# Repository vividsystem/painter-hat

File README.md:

# painter-hat
## A stepper motor hat that sucks less.
<div style="display: flex; flex-direction: row;">

</div>

Disclaimer: I haven't gotten the possibility to actually manufacture this yet. Therefore it might not work

Features:
* dual stepper-motor driver control <br>
* 100W USB-C PD to power motors and raspberry pi <br>
* support for A4988, TMC2208, TMC2209, etc. driver modules including UART control <br>
* meant as a replacement for [Waveshare Stepper Motor HAT](https://www.waveshare.com/wiki/Stepper_Motor_HAT)<sup>*</sup> <br><br><br>

<sup>*</sup>not completely hot-swap. you will have to use a different firmware

## Motivation 
I was very frustrated working with the [Waveshare Stepper Motor HAT](https://www.waveshare.com/wiki/Stepper_Motor_HAT).
The quality control seems to be off as two HATs I ordered didn't work. 
Their documentation is good and the provided codes works but there are some minor issues that led me to write my own code to
control the hat. Most importantly you can't swap drivers (in case you fry them for example) which led me to buy multiple
new drivers after testing and subsequently frying the drivers. This sucks because for my use case I have to get a whole
new HAT even when one of the two drivers is still working.

## Schematic

## PCB
### Top Layer - Signal

### 1st Internal Layer - Ground 

### 2nd Internal Layer - Power 

### Bottom Layer - Signal with GND Copper Fill 

## DIY it
It is about 155.58€ for the minimum PCBA PCB amount on JLCPCB.

## Firmware
Currently outdated!

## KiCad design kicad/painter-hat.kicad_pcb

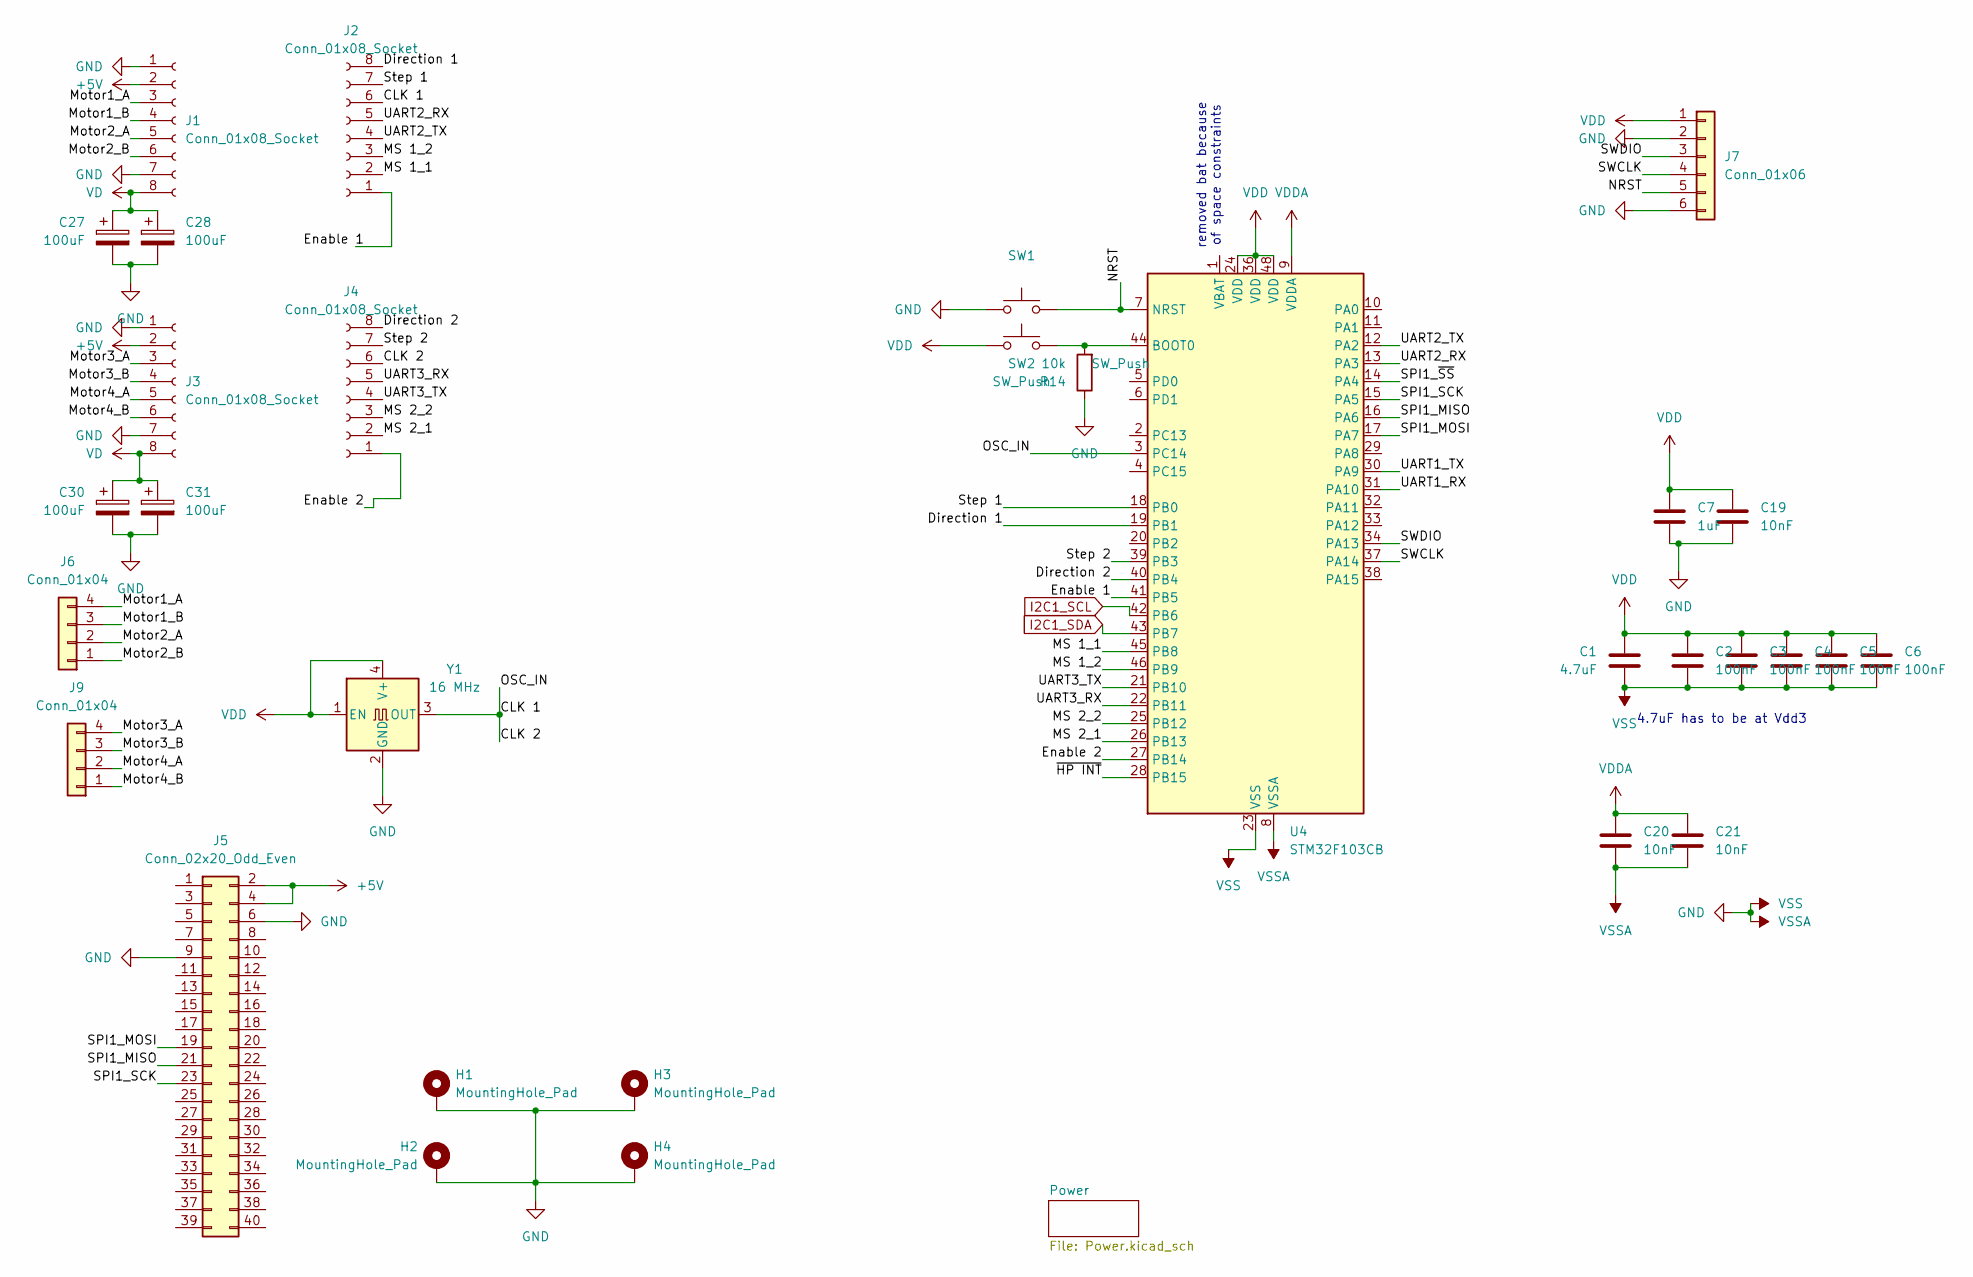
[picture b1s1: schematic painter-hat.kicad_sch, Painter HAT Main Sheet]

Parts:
C1: 4.7uF; C_0603_1608Metric
C2, C3, C4, C5, C6: 100nF; C_0402_1005Metric
C7: 1uF; C_0402_1005Metric
C19, C20, C21: 10nF; C_0402_1005Metric
C27, C28, C30, C31: 100uF; C_Elec_8x10.2
H1, H2, H3, H4: MountingHole_Pad; MountingHole_2.7mm_M2.5_DIN965_Pad_TopBottom
J1, J2, J3, J4: Conn_01x08_Socket; PinSocket_1x08_P2.54mm_Vertical
J5: Conn_02x20_Odd_Even; PinHeader_2x20_P2.54mm_Vertical
J6, J9: Conn_01x04; JST_XH_B4B-XH-AM_1x04_P2.50mm_Vertical
J7: Conn_01x06; PinSocket_1x06_P2.54mm_Vertical
R14: 10k; R_0402_1005Metric
SW1, SW2: SW_Push; SW_Push_1P1T_NO_CK_KMR2
U4: STM32F103CB; LQFP-48_7x7mm_P0.5mm
Y1: 16 MHz; Oscillator_SMD_EuroQuartz_XO91-4Pin_7.0x5.0mm

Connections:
+5V: J1.2, J3.2, J5.2, J5.4; also elsewhere on the board
/CLK 1: J2.6, J4.6, U4.3 (PC14), Y1.3 (OUT)
/Direction 1: J2.8, U4.19 (PB1)
/Direction 2: J4.8, U4.40 (PB4)
/Enable 1: J2.1, U4.41 (PB5)
/Enable 2: J4.1, U4.27 (PB14)
/MS 1_1: J2.2, U4.45 (PB8)
/MS 1_2: J2.3, U4.46 (PB9)
/MS 2_1: J4.2, U4.26 (PB13)
/MS 2_2: J4.3, U4.25 (PB12)
/Motor1_A: J1.3, J6.4
/Motor1_B: J1.4, J6.3
/Motor2_A: J1.5, J6.2
/Motor2_B: J1.6, J6.1
/Motor3_A: J3.3, J9.4
/Motor3_B: J3.4, J9.3
/Motor4_A: J3.5, J9.2
/Motor4_B: J3.6, J9.1
/NRST: J7.5, SW1.2, U4.7 (NRST)
/SPI1_MISO: J5.21, U4.16 (PA6)
/SPI1_MOSI: J5.19, U4.17 (PA7)
/SPI1_SCK: J5.23, U4.15 (PA5)
/SPI1_~SS: U4.14 (PA4)
/SWCLK: J7.4, U4.37 (PA14)
/SWDIO: J7.3, U4.34 (PA13)
/Step 1: J2.7, U4.18 (PB0)
/Step 2: J4.7, U4.39 (PB3)
/UART1_RX: U4.31 (PA10)
/UART1_TX: U4.30 (PA9)
/UART2_RX: J2.5, U4.13 (PA3)
/UART2_TX: J2.4, U4.12 (PA2)
/UART3_RX: J4.5, U4.22 (PB11)
/UART3_TX: J4.4, U4.21 (PB10)
/~HP INT: U4.28 (PB15)
GND: C1.2, C2.2, C3.2, C4.2, C5.2, C6.2, C7.2, C19.2, C20.2, C21.2, C27.2, C28.2, C30.2, C31.2, H1.1, H2.1, H3.1, H4.1, J1.1, J1.7, J3.1, J3.7, J5.6, J5.9, J7.2, J7.6, R14.1, SW1.1, U4.8 (VSSA), U4.23 (VSS), U4.35 (VSS), U4.47 (VSS), Y1.2 (GND); also elsewhere on the board
I2C1_SCL: U4.42 (PB6); also elsewhere on the board
I2C1_SDA: U4.43 (PB7); also elsewhere on the board
unnamed: R14.2, SW2.2, U4.44 (BOOT0)
VD: C27.1, C28.1, C30.1, C31.1, J1.8, J3.8; also elsewhere on the board
VDD: C1.1, C2.1, C3.1, C4.1, C5.1, C6.1, C7.1, C19.1, C20.1, C21.1, J7.1, SW2.1, U4.9 (VDDA), U4.24 (VDD), U4.36 (VDD), U4.48 (VDD), Y1.1 (EN), Y1.4 (V+); also elsewhere on the board

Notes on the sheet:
4.7uF has to be at Vdd3
removed bat because of space constraints

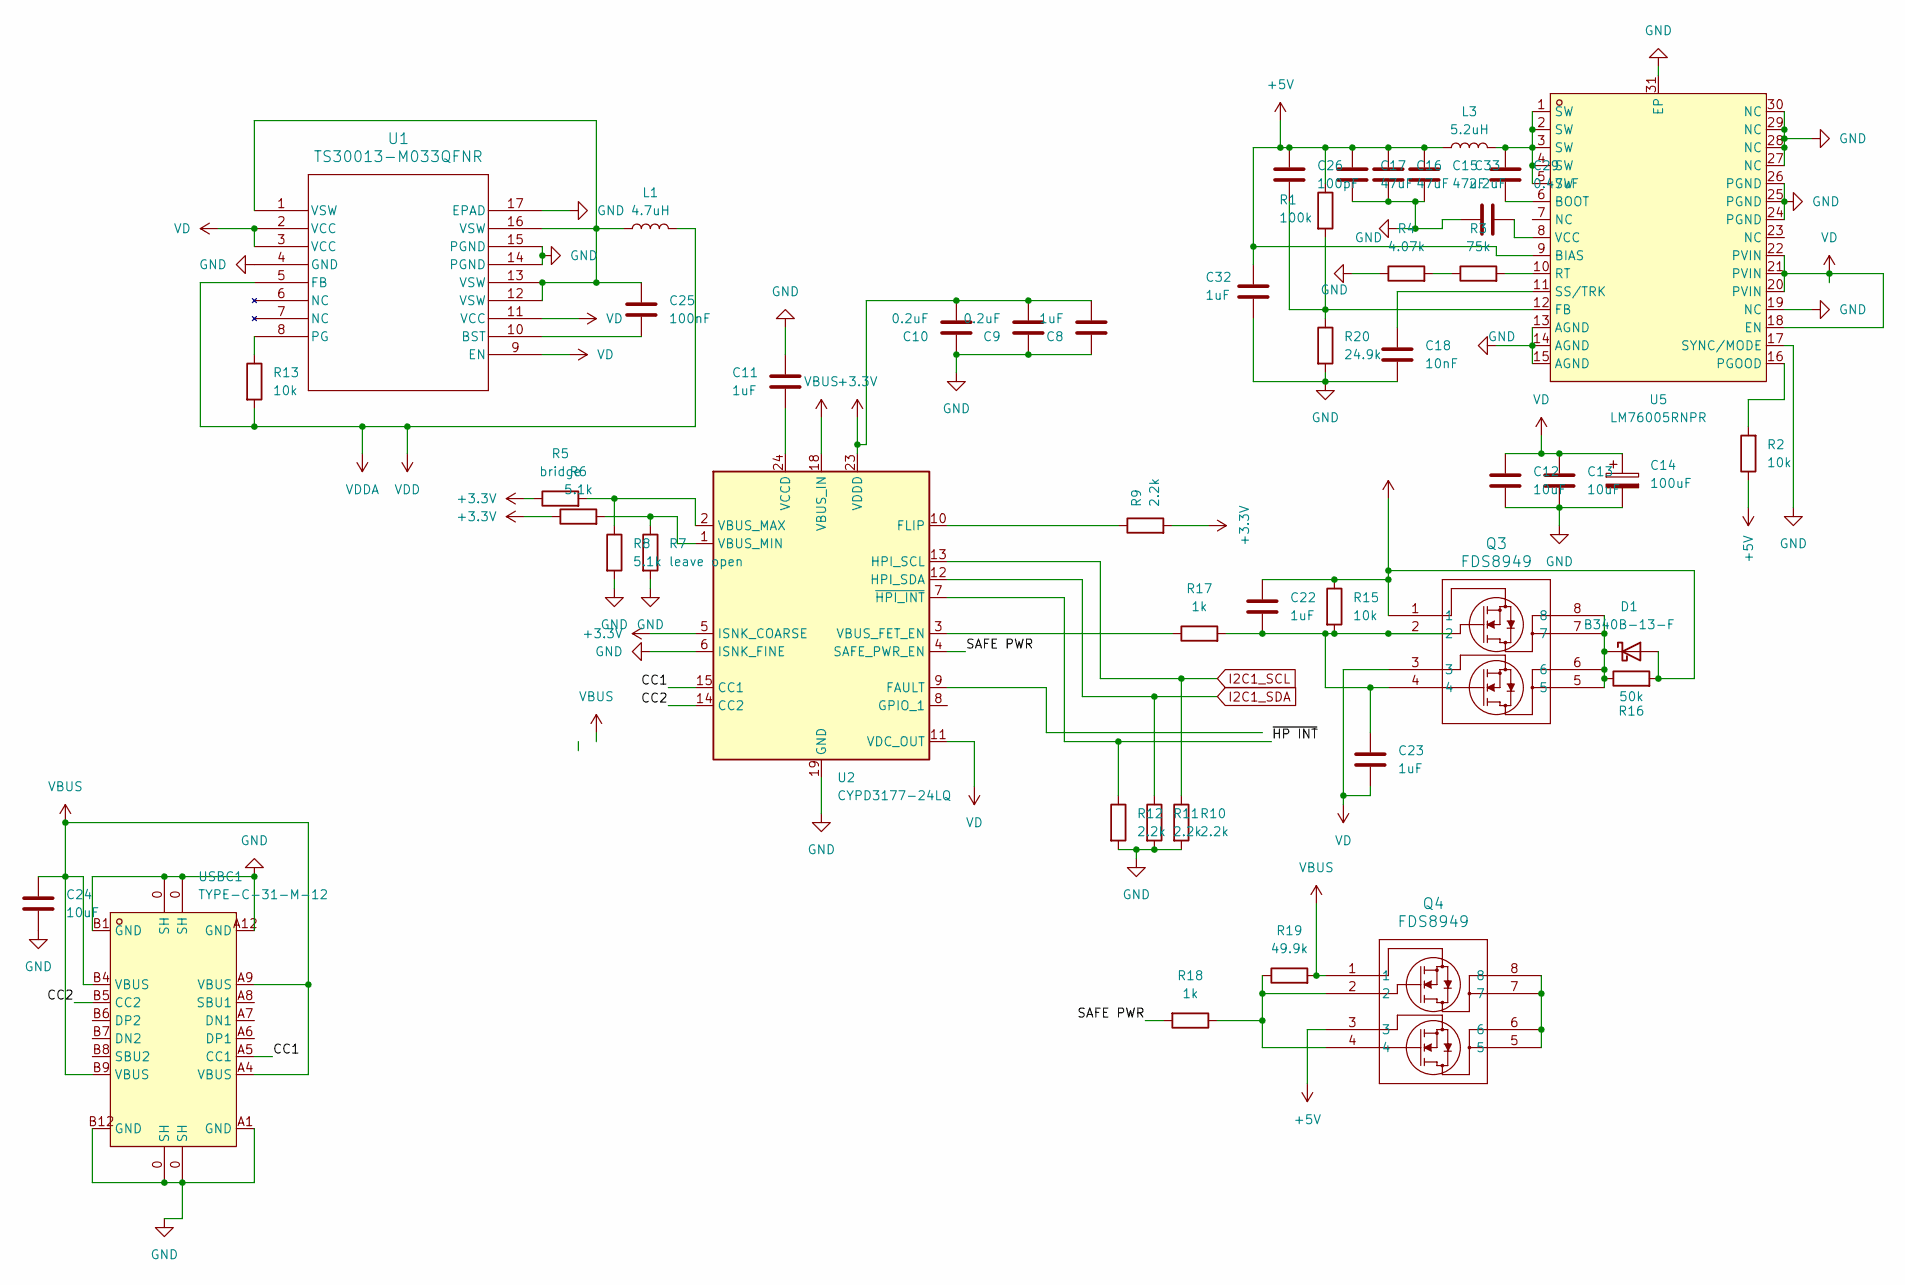
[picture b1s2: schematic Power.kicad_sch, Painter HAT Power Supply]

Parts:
C8, C11, C32: 1uF; C_0402_1005Metric
C9, C10: 0.2uF; C_0402_1005Metric
C12, C13, C24: 10uF; C_0805_2012Metric
C14: 100uF; C_Elec_8x10.2
C15, C16, C17: 47uF; C_0805_2012Metric
C18: 10nF; C_0402_1005Metric
C22, C23: 1uF; C_0805_2012Metric
C25: 100nF; R_0402_1005Metric
C26: 100pF; C_0402_1005Metric
C29: 0.47uF; C_0402_1005Metric
C33: 2.2uF; C_0402_1005Metric
D1: B340B-13-F; D_SMB
L1: 4.7uH; IND_NRS5030T100MMGJ_TAY
L3: 5.2uH; IND-SMD_4P-L10.5-W9.5-TL
Q3, Q4: FDS8949; SOIC8_3P9X4P9_OSI
R1: 100k; R_0603_1608Metric
R2, R13: 10k; R_0402_1005Metric
R3: 75k; R_0603_1608Metric
R4: 4.07k; R_0603_1608Metric
R5: bridge; R_0402_1005Metric
R6, R8: 5.1k; R_0402_1005Metric
R7: leave open; R_0402_1005Metric
R9, R10, R11, R12: 2.2k; R_0402_1005Metric
R15: 10k; C_0603_1608Metric
R16: 50k; R_0603_1608Metric
R17: 1k; C_0603_1608Metric
R18: 1k; R_0402_1005Metric
R19: 49.9k; R_0402_1005Metric
R20: 24.9k; R_0603_1608Metric
U1: TS30013-M033QFNR; QFN16_3X3_SEM
U2: CYPD3177-24LQ; QFN-24-1EP_4x4mm_P0.5mm_EP2.75x2.75mm
U5: LM76005RNPR; WQFN-30_L6.0-W4.0-P0.50-TL-EP_LM76005RNPR; LCSC Part C2866241
USBC1: TYPE-C-31-M-12; USB-C_SMD-TYPE-C-31-M-12; LCSC Part C165948

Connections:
+3.3V: C8.1, C9.2, C10.2, R5.1, R6.1, R9.2, U2.5 (ISNK_COARSE), U2.23 (VDDD)
+5V: C15.1, C16.1, C17.1, C26.1, C32.2, L3.1, Q4.3, R1.1, R2.1, U5.9 (BIAS); also elsewhere on the board
/Power/CC1: U2.15 (CC1), USBC1.A5 (CC1)
/Power/CC2: U2.14 (CC2), USBC1.B5 (CC2)
/Power/SAFE PWR: R18.2, U2.4 (SAFE_PWR_EN)
/Power/~HP INT: R12.1, U2.7 (~HPI_INT)
GND: C8.2, C9.1, C10.1, C11.1, C12.2, C13.2, C14.2, C15.2, C16.2, C17.2, C18.2, C24.1, C32.1, C33.1, R4.1, R7.2, R8.2, R10.2, R11.2, R12.2, R20.2, U1.4 (GND), U1.14 (PGND), U1.15 (PGND), U1.17 (EPAD), U2.6 (ISNK_FINE), U2.19 (GND), U2.22 (GND), U2.25 (GND), U5.13 (AGND), U5.14 (AGND), U5.15 (AGND), U5.17 (SYNC/MODE), U5.19 (NC), U5.24 (PGND), U5.25 (PGND), U5.26 (PGND), U5.27 (NC), U5.28 (NC), U5.29 (NC), U5.30 (NC), U5.31 (EP), USBC1.0 (SH), USBC1.1, USBC1.2, USBC1.3, USBC1.A1 (GND), USBC1.A12 (GND), USBC1.B1 (GND), USBC1.B12 (GND); also elsewhere on the board
I2C1_SCL: R10.1, U2.13 (HPI_SCL); also elsewhere on the board
I2C1_SDA: R11.1, U2.12 (HPI_SDA); also elsewhere on the board
unnamed: C22.2, C23.1, Q3.2, Q3.4, R15.2, R17.2
unnamed: C25.1, L1.1, U1.1 (VSW), U1.12 (VSW), U1.13 (VSW), U1.16 (VSW)
unnamed: C29.2, L3.2, U5.1 (SW), U5.2 (SW), U5.3 (SW), U5.4 (SW), U5.5 (SW)
unnamed: D1.1 (K), Q3.5, Q3.6, Q3.7, Q3.8, R16.1
unnamed: Q4.2, Q4.4, R18.1, R19.1
unnamed: Q4.5, Q4.6, Q4.7, Q4.8
unnamed: R3.1, R4.2
unnamed: C25.2, U1.10 (BST)
unnamed: R13.1, U1.8 (PG)
unnamed: R9.1, U2.10 (FLIP)
unnamed: R17.1, U2.3 (VBUS_FET_EN)
unnamed: R5.2, R8.1, U2.2 (VBUS_MAX)
unnamed: R6.2, R7.1, U2.1 (VBUS_MIN)
unnamed: C11.2, U2.24 (VCCD)
unnamed: C29.1, U5.6 (BOOT)
unnamed: C26.2, R1.2, R20.1, U5.12 (FB)
unnamed: R2.2, U5.16 (PGOOD)
unnamed: R3.2, U5.10 (RT)
unnamed: C18.1, U5.11 (SS/TRK)
unnamed: C33.2, U5.8 (VCC)
VBUS: C22.1, C24.2, D1.2 (A), Q3.1, Q4.1, R15.1, R16.2, R19.2, U2.18 (VBUS_IN), USBC1.A4 (VBUS), USBC1.A9 (VBUS), USBC1.B4 (VBUS), USBC1.B9 (VBUS)
VD: C12.1, C13.1, C14.1, C23.2, Q3.3, U1.2 (VCC), U1.3 (VCC), U1.9 (EN), U1.11 (VCC), U2.11 (VDC_OUT), U5.18 (EN), U5.20 (PVIN), U5.21 (PVIN), U5.22 (PVIN); also elsewhere on the board
VDD: L1.2, R13.2, U1.5 (FB); also elsewhere on the board

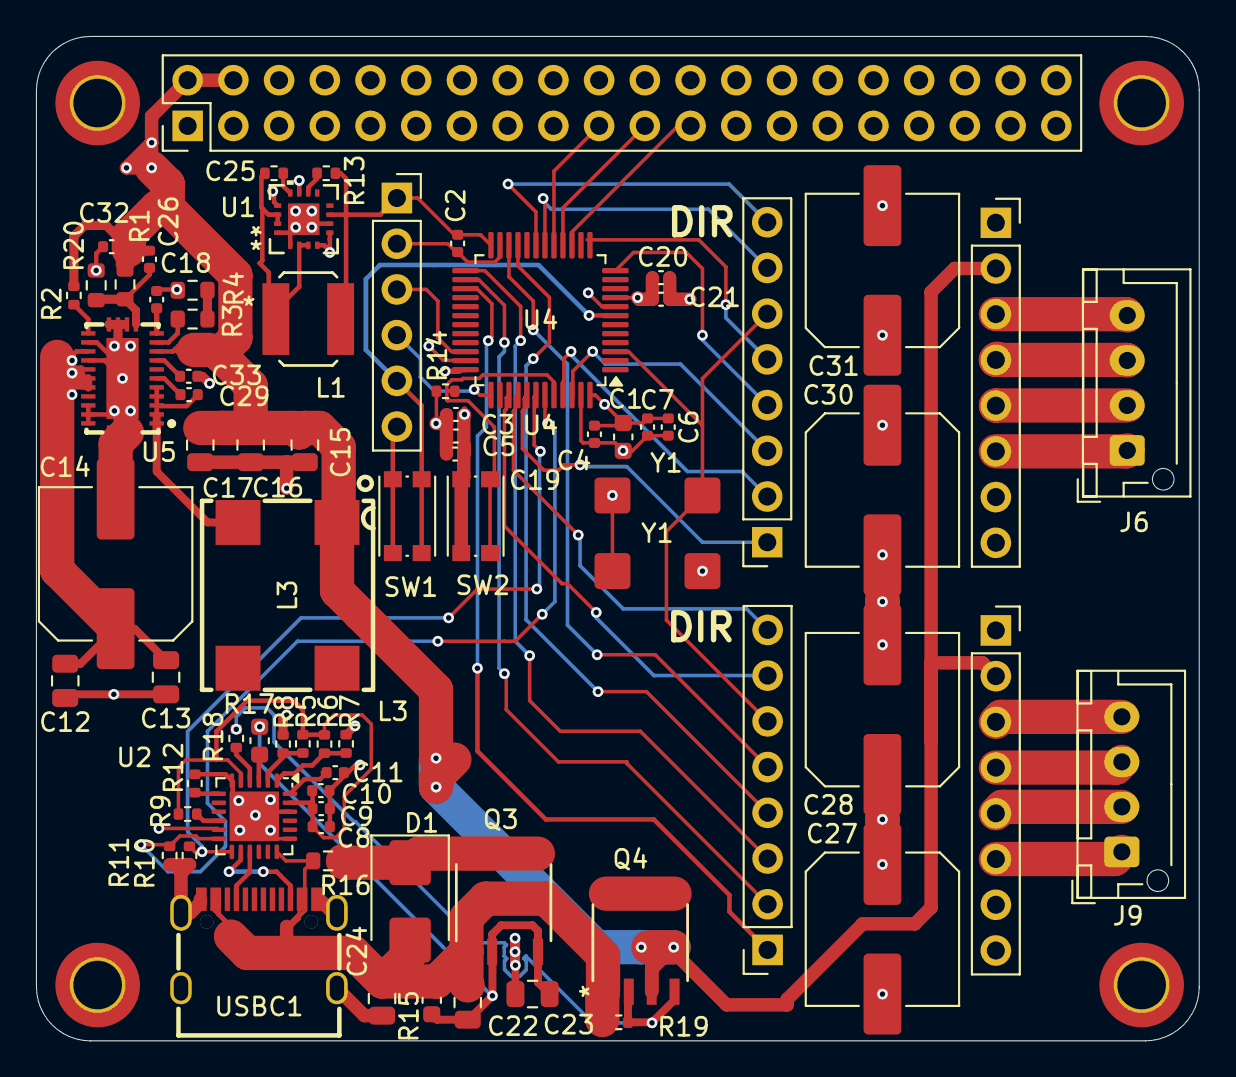
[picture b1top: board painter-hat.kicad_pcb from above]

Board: 4 copper layers, 64.6 x 55.8 mm, 78 parts (0 on the bottom side), 62 nets.

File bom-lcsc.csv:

"Id";"Designator";"Footprint";"Quantity";"Designation";"Supplier and ref";
1;"U2";"QFN-24-1EP_4x4mm_P0.5mm_EP2.75x2.75mm";1;"CYPD3177-24LQ";"C2959321";;
2;"SW2,SW1";"SW_Push_1P1T_NO_CK_KMR2";2;"SW_Push";"C221679";;
3;"J10";"SAMESKY_UJ40-C-H-G-SMT-P24-TR";1;"UJ40-C-H-G-SMT-P24-TR";"C6006461";;
4;"R17";"C_0603_1608Metric";1;"1k";"C2653986";;
5;"C17,C13,C1";"C_0603_1608Metric";3;"4.7uF";C162274;;
6;"R10,R9,R12,R11";"R_0402_1005Metric";4;"2.2k";"C82680";;
7;"C3,C5,C2,C4,C6,C25";"C_0402_1005Metric";5;"100nF";"C22333701";;
8;"L2";"L_Coilcraft_XxL4030";1;"3.3-4.7uH";C19191629;;
9;"R15";"C_0603_1608Metric";1;"10k";"C327830";;
10;"U4";"LQFP-48_7x7mm_P0.5mm";1;"STM32F103CB";"C8304";;
11;"J1,J2,J3,J4";"PinSocket_1x08_P2.54mm_Vertical";4;"Conn_01x08_Socket";"C27438";;
12;"J7";"PinSocket_1x06_P2.54mm_Vertical";1;"Conn_01x06";"C40877";;
13;"R18";"R_0402_1005Metric";1;"1k";"C4162025";;
14;"Y2";"Oscillator_SMD_EuroQuartz_XO91-4Pin_7.0x5.0mm";1;"16 MHz";"C596923";;
15;"R6,R8";"R_0402_1005Metric";2;"5.1k";"C6221081";;
16;"C14,C16,C15";"C_0805_2012Metric";3;"22uF";"C3853399.html";;
17;"C19,C20,C21";"C_0402_1005Metric";3;"10nF";"C85735.html";;
18;"D1";"D_SMB";1;"onsemi SS34";"C154551.html";;
19;"C9,C10";"C_0402_1005Metric";2;"0.2uF";"C2180912";;
20;"U1";"QFN16_3X3_SEM";1;"TS30013-M033QFNR";"C2071049";;
21;"J9,J6";"JST_XH_B4B-XH-AM_1x04_P2.50mm_Vertical";2;"Conn_01x04";"C161871";;
22;"C24";"C_0805_2012Metric";1;"10uF";"C22051142";;
23;"C18,C26";"C_0603_1608Metric";2;"2.2uF";"C710921";;
24;"J5";"PinHeader_2x20_P2.54mm_Vertical";1;"Conn_02x20_Odd_Even";"C306217";;
25;"R13,R14";"R_0402_1005Metric";2;"10k";"C7501196";;
26;"Q3,Q4";"SOIC8_3P9X4P9_OSI";2;"FDS8949";"C10874";;
27;"L1";"IND_NRS5030T100MMGJ_TAY";1;"4.7uH";"C2880386";;
28;"C12";"C_0603_1608Metric";1;"10uF";"C194427";;
29;"C22,C23";"C_0805_2012Metric";2;"1uF";"C28323";;
30;"R19";"R_0402_1005Metric";1;"49.9k";"C4043528";;
31;"C8,C11,C7";"C_0402_1005Metric";3;"1uF";"C5596482";;
32;"U3";"FC2QFN-17";1;"MAX26405AFOAY+T";"https://www.mouser.de/ProductDetail/Analog-Devices-Maxim-Int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";;
33;"R16";"R_0603_1608Metric";1;"50k";"C2073717";;

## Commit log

2025-07-31 inital commit
2025-07-31 feat(hw): basic wiring done
2025-07-31 added firmware
2025-07-31 finalized pcb
2025-08-05 feat: added bom
2025-08-05 feat: v2
2025-08-05 fix: minor additions to v2
2025-08-06 docs: bom with lcsc part numbers
2025-08-06 feat: v2.1
2025-08-06 feat: updated everything
2025-08-06 pretty readme
2025-08-06 fix: updated pcb picture
2025-08-06 feat: pcb screens
2025-08-06 feat: added jlcpcb bom
2025-08-07 feat: added image path to .gitignore
2025-08-07 feat(v2.1.1): BOOT0, NRST Wiring, Polarized Caps fixed
2025-08-07 docs: beautiful README
2025-08-07 feat: image display fixed
2025-08-07 fix: .gitignore
2025-08-07 feat: added schematic images these were previously not added due to the misconfigured .gitignore
2025-08-07 docs: changed README contents order
2025-08-07 docs: fixed GH List rendering
2025-08-08 feat: added community designs
